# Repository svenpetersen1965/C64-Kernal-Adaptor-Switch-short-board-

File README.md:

# C64 Kernel Switch    [![Badge License]][License]    [![Badge Price]][Price]

*An Adapter For **[ASSY250469]**, The 'Short Board'.*

<br>
<br>

Since the **BASIC** is stored in the same **ROM**, <br>
some circuit is required that allows for stable <br>
access to **BASIC**, while the Kernel is selected.

The kernel selection can be configured with <br>
either some jumpers, a switch or even using <br>
a micro controller.

*For this purpose, `+5V` are* <br>
*provided on the pin header.*

<br>
<br>

## Inspiration

This development was inspired by **Adrian Black's** YouTube video: <br>
    *[How - To: C64 Arduino based Restore Key / Four Kernal Switcher / Hard Reset][Video]*

<br>
<br>

# Revision 2

This revision provides an optional pin <br>
header with the address bit `A5` + `A8` <br>
for stereo **SID** applications.

<br>

<!----------------------------------------------------------------------------->

[ASSY250469]: https://support.retrorewind.ca/commodore/c64/assy-250469
[Video]: https://youtu.be/GPq5xnJRw2w

[License]: #
[Price]: Revisions/0/Excel '1. Calculation From BOM Of Rev. 0&#10;2. Component Prices May Have Changed&#10;3. Shipping fees not included'

<!---------------------------------{ Badges }---------------------------------->

[Badge License]: https://img.shields.io/badge/License-GPL_3-blue.svg?style=for-the-badge
[Badge Price]: https://img.shields.io/badge/Estimated_Price-4.88€-37a779?style=for-the-badge

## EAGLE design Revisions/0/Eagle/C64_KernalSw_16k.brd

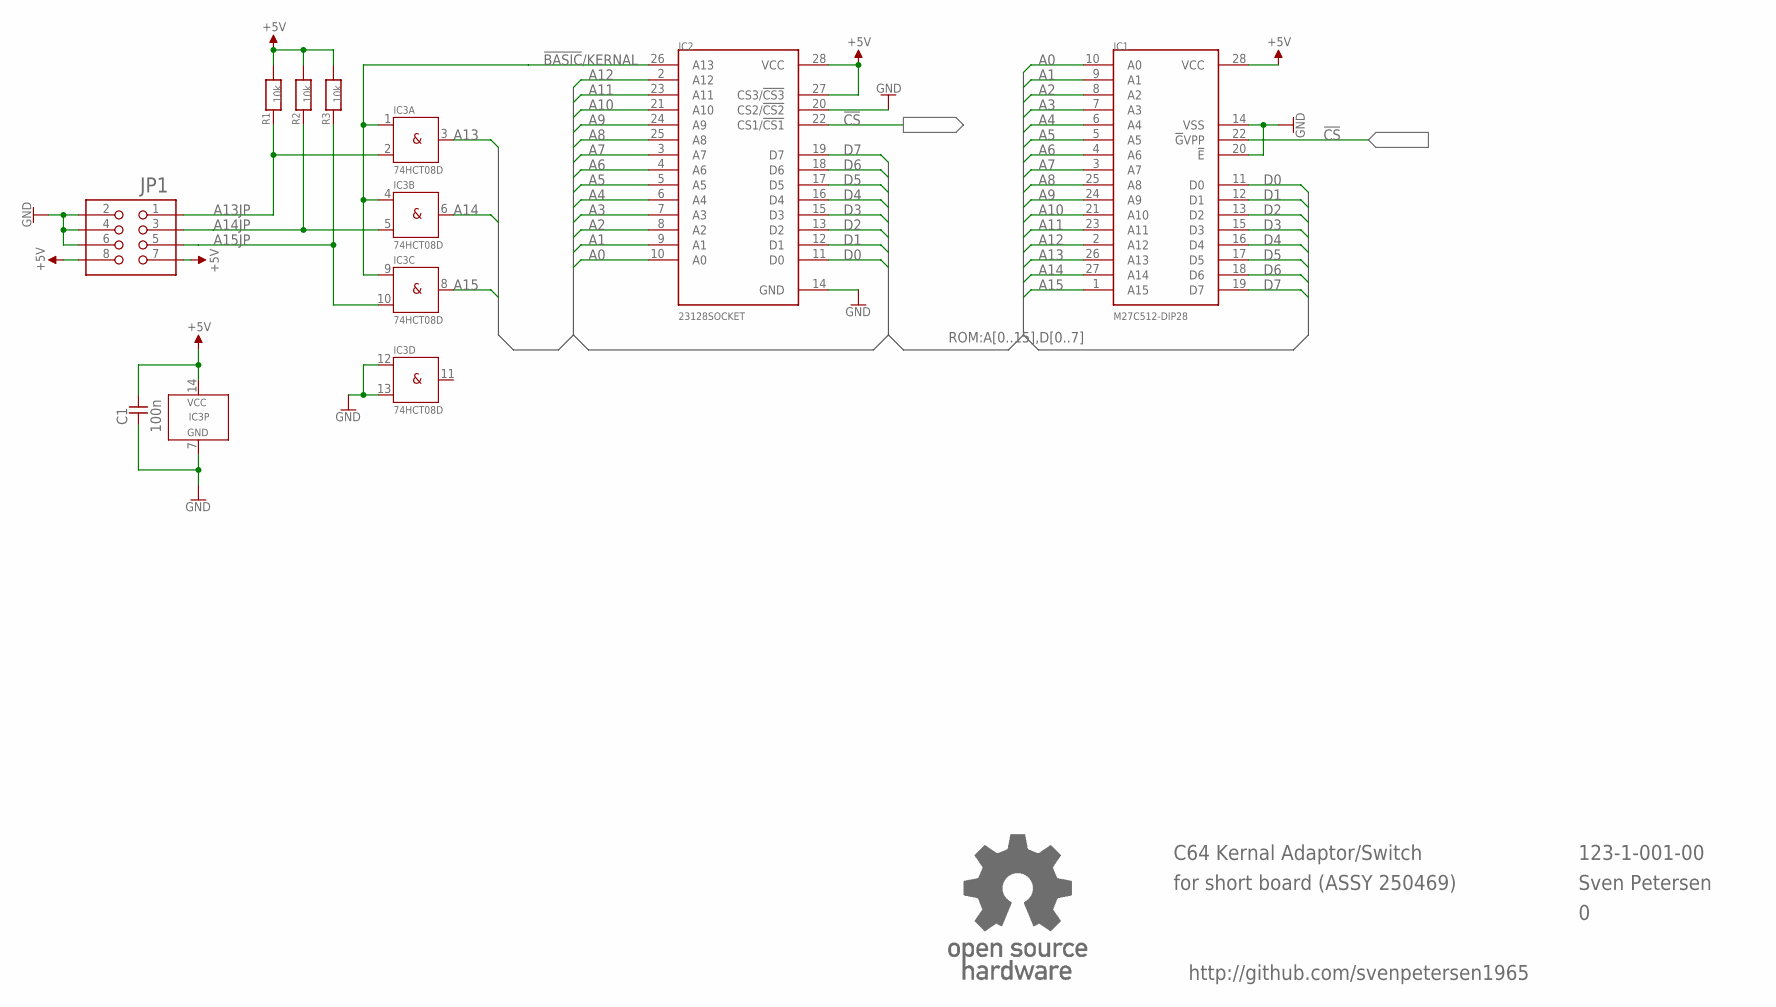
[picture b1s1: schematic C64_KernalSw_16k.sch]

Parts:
C1: 100n; 0805
IC1: M27C512-DIP28; DIL28-6
IC2: 23128SOCKET; DIL28_SOCKET
IC3: 74HCT08D; SO-14
JP1: PINHD-2X490°/MPE_088; 2X04_90_SERIES_088
R1, R2, R3: 10k; 0805
U$21: OPEN_SOURCE_HW; OPENHW

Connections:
!BASIC!/KERNAL: IC2.26 (A13), IC3.1 (I0), IC3.4 (I0), IC3.9 (I0)
!CS: IC1.22 (!G!VPP), IC2.22 (CS1/!CS1)
+5V: C1.2, IC1.28 (VCC), IC2.27 (CS3/!CS3), IC2.28 (VCC), IC3.14 (VCC), JP1.7, JP1.8, R1.2, R2.2, R3.2
A0: IC1.10 (A0), IC2.10 (A0)
A1: IC1.9 (A1), IC2.9 (A1)
A2: IC1.8 (A2), IC2.8 (A2)
A3: IC1.7 (A3), IC2.7 (A3)
A4: IC1.6 (A4), IC2.6 (A4)
A5: IC1.5 (A5), IC2.5 (A5)
A6: IC1.4 (A6), IC2.4 (A6)
A7: IC1.3 (A7), IC2.3 (A7)
A8: IC1.25 (A8), IC2.25 (A8)
A9: IC1.24 (A9), IC2.24 (A9)
A10: IC1.21 (A10), IC2.21 (A10)
A11: IC1.23 (A11), IC2.23 (A11)
A12: IC1.2 (A12), IC2.2 (A12)
A13: IC1.26 (A13), IC3.3 (O)
A13JP: IC3.2 (I1), JP1.1, R1.1
A14: IC1.27 (A14), IC3.6 (O)
A14JP: IC3.5 (I1), JP1.3, R2.1
A15: IC1.1 (A15), IC3.8 (O)
A15JP: IC3.10 (I1), JP1.5, R3.1
D0: IC1.11 (D0), IC2.11 (D0)
D1: IC1.12 (D1), IC2.12 (D1)
D2: IC1.13 (D2), IC2.13 (D2)
D3: IC1.15 (D3), IC2.15 (D3)
D4: IC1.16 (D4), IC2.16 (D4)
D5: IC1.17 (D5), IC2.17 (D5)
D6: IC1.18 (D6), IC2.18 (D6)
D7: IC1.19 (D7), IC2.19 (D7)
GND: C1.1, IC1.14 (VSS), IC1.20 (!E), IC2.14 (GND), IC2.20 (CS2/!CS2), IC3.7 (GND), IC3.12 (I0), IC3.13 (I1), JP1.2, JP1.4, JP1.6

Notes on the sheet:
123-1-001-00
Sven Petersen
C64 Kernal Adaptor/Switch
for short board (ASSY 250469)
http://github.com/svenpetersen1965

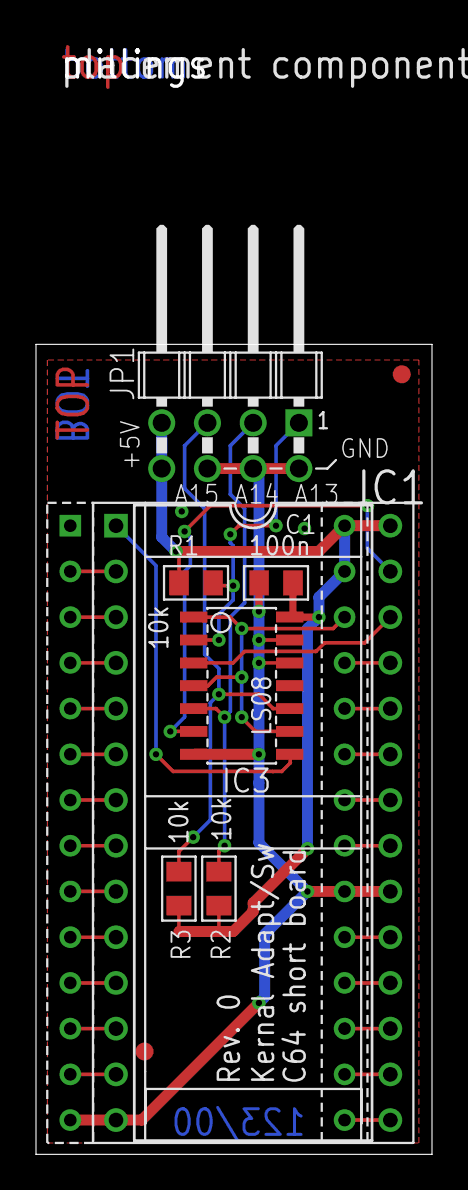
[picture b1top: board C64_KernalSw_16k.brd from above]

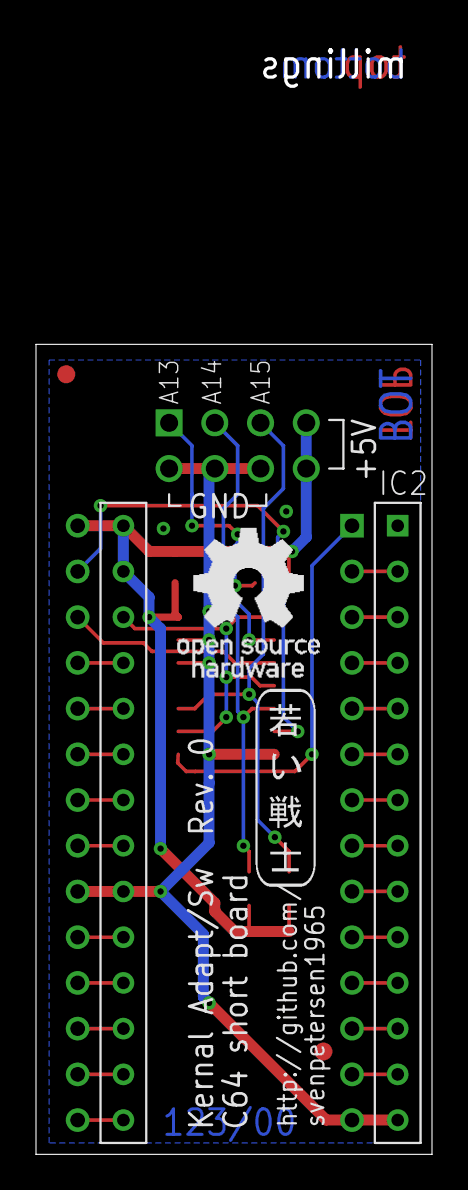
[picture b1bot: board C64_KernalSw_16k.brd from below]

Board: 2 copper layers, 22.0 x 45.0 mm, 15 parts (2 on the bottom side), 31 nets.

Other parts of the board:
U$16: GS28P
U$17, U$18: SMD_REF_R1MM
U$19: 2LAYER
U$20: PCB-TITLE/
U$22: SVEN_TAG

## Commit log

2020-06-09 BOM calculation added
    prices of June 9th, 2020
2020-08-07 Silk Screen Update
2020-08-16 picknplace in mm and inch
2022-02-25 Rev. 1 released
2022-02-25 Rev. 2 released
2022-05-29 Moved Revisions Into Revision Folder
2022-05-29 README Formatting
2022-05-29 Added Price Badge
2022-05-29 Added License Badge
2022-05-29 Formatted Revision Section
2022-05-29 Formatted Description
2022-05-29 Adjusted Spacing
2022-05-29 Fixed Layout
